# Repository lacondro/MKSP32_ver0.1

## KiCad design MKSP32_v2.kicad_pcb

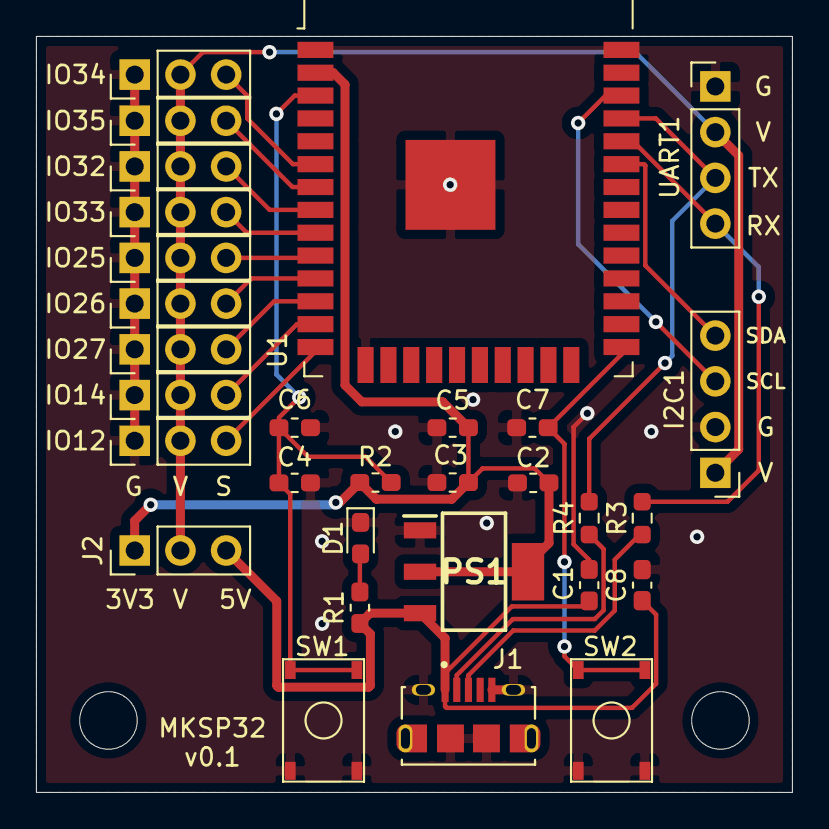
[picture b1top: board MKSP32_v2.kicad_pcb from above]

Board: 2 copper layers, 42.0 x 42.0 mm, 30 parts (0 on the bottom side), 22 nets.

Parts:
C1, C2, C3: 22uF/10V; C_0603_1608Metric_Pad1.05x0.95mm_HandSolder
C4, C5, C6, C7: 0.1uF/50V; C_0603_1608Metric_Pad1.05x0.95mm_HandSolder
C8: 0.1uF; C_0603_1608Metric_Pad1.08x0.95mm_HandSolder
D1: LED; LED_0603_1608Metric_Pad1.05x0.95mm_HandSolder
I2C1: Conn_01x04_Male; PinHeader_1x04_P2.54mm_Vertical
IO12, IO14, IO25, IO26, IO27, IO32, IO33, IO34, IO35: Conn_01x03_Male; PinHeader_1x03_P2.54mm_Vertical
J1: 10118194-0001LF; AMPHENOL_10118194-0001LF
J2: Conn_01x03_Male; PinHeader_1x03_P2.54mm_Vertical
PS1: ZLDO1117QG33TA; SOT230P700X180-4N
R1: 2K; R_0603_1608Metric_Pad1.05x0.95mm_HandSolder
R2: 10K; R_0603_1608Metric_Pad1.05x0.95mm_HandSolder
R3, R4: 1k; R_0603_1608Metric_Pad0.98x0.95mm_HandSolder
SW1, SW2: SW_DPST; NW3-A06-C1
U1: ESP32-WROOM-32
UART1: Conn_01x04_Male; PinHeader_1x04_P2.54mm_Vertical

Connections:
3V3: C2.1, C3.1, C5.1, J2.1, PS1.2, PS1.4, R2.1, U1.2
5V: C1.1, C8.1, J1.1, J2.3, PS1.3, R1.1
EN: C4.1, C6.1, R2.2, SW1.2, SW1.4, U1.3
GND: C1.2, C2.2, C3.2, C4.2, C5.2, C6.2, C7.2, C8.2, D1.1, I2C1.2, IO12.1, IO14.1, IO25.1, IO26.1, IO27.1, IO32.1, IO33.1, IO34.1, IO35.1, J1.5, J1.S1, J1.S2, J1.S3, J1.S4, J1.S5, J1.S6, PS1.1, SW1.1, SW1.3, SW2.1, SW2.3, U1.1, U1.15, U1.38, U1.39, UART1.1
IO0: C7.1, SW2.2, SW2.4, U1.25
IO12: IO12.3, U1.14
IO14: IO14.3, U1.13
IO21: I2C1.4, U1.33
IO22: I2C1.3, U1.36
IO25: IO25.3, U1.10
IO26: IO26.3, U1.11
IO27: IO27.3, U1.12
IO32: IO32.3, U1.8
IO33: IO33.3, U1.9
IO34: IO34.3, U1.6
IO35: IO35.3, U1.7
unnamed: D1.2, R1.2
unnamed: J1.2, R4.1
unnamed: J1.3, R3.2
RXD0: R3.1, U1.34, UART1.4
TXD0: R4.2, U1.35, UART1.3
VBUS: I2C1.1, IO12.2, IO14.2, IO25.2, IO26.2, IO27.2, IO32.2, IO33.2, IO34.2, IO35.2, J2.2, UART1.2
